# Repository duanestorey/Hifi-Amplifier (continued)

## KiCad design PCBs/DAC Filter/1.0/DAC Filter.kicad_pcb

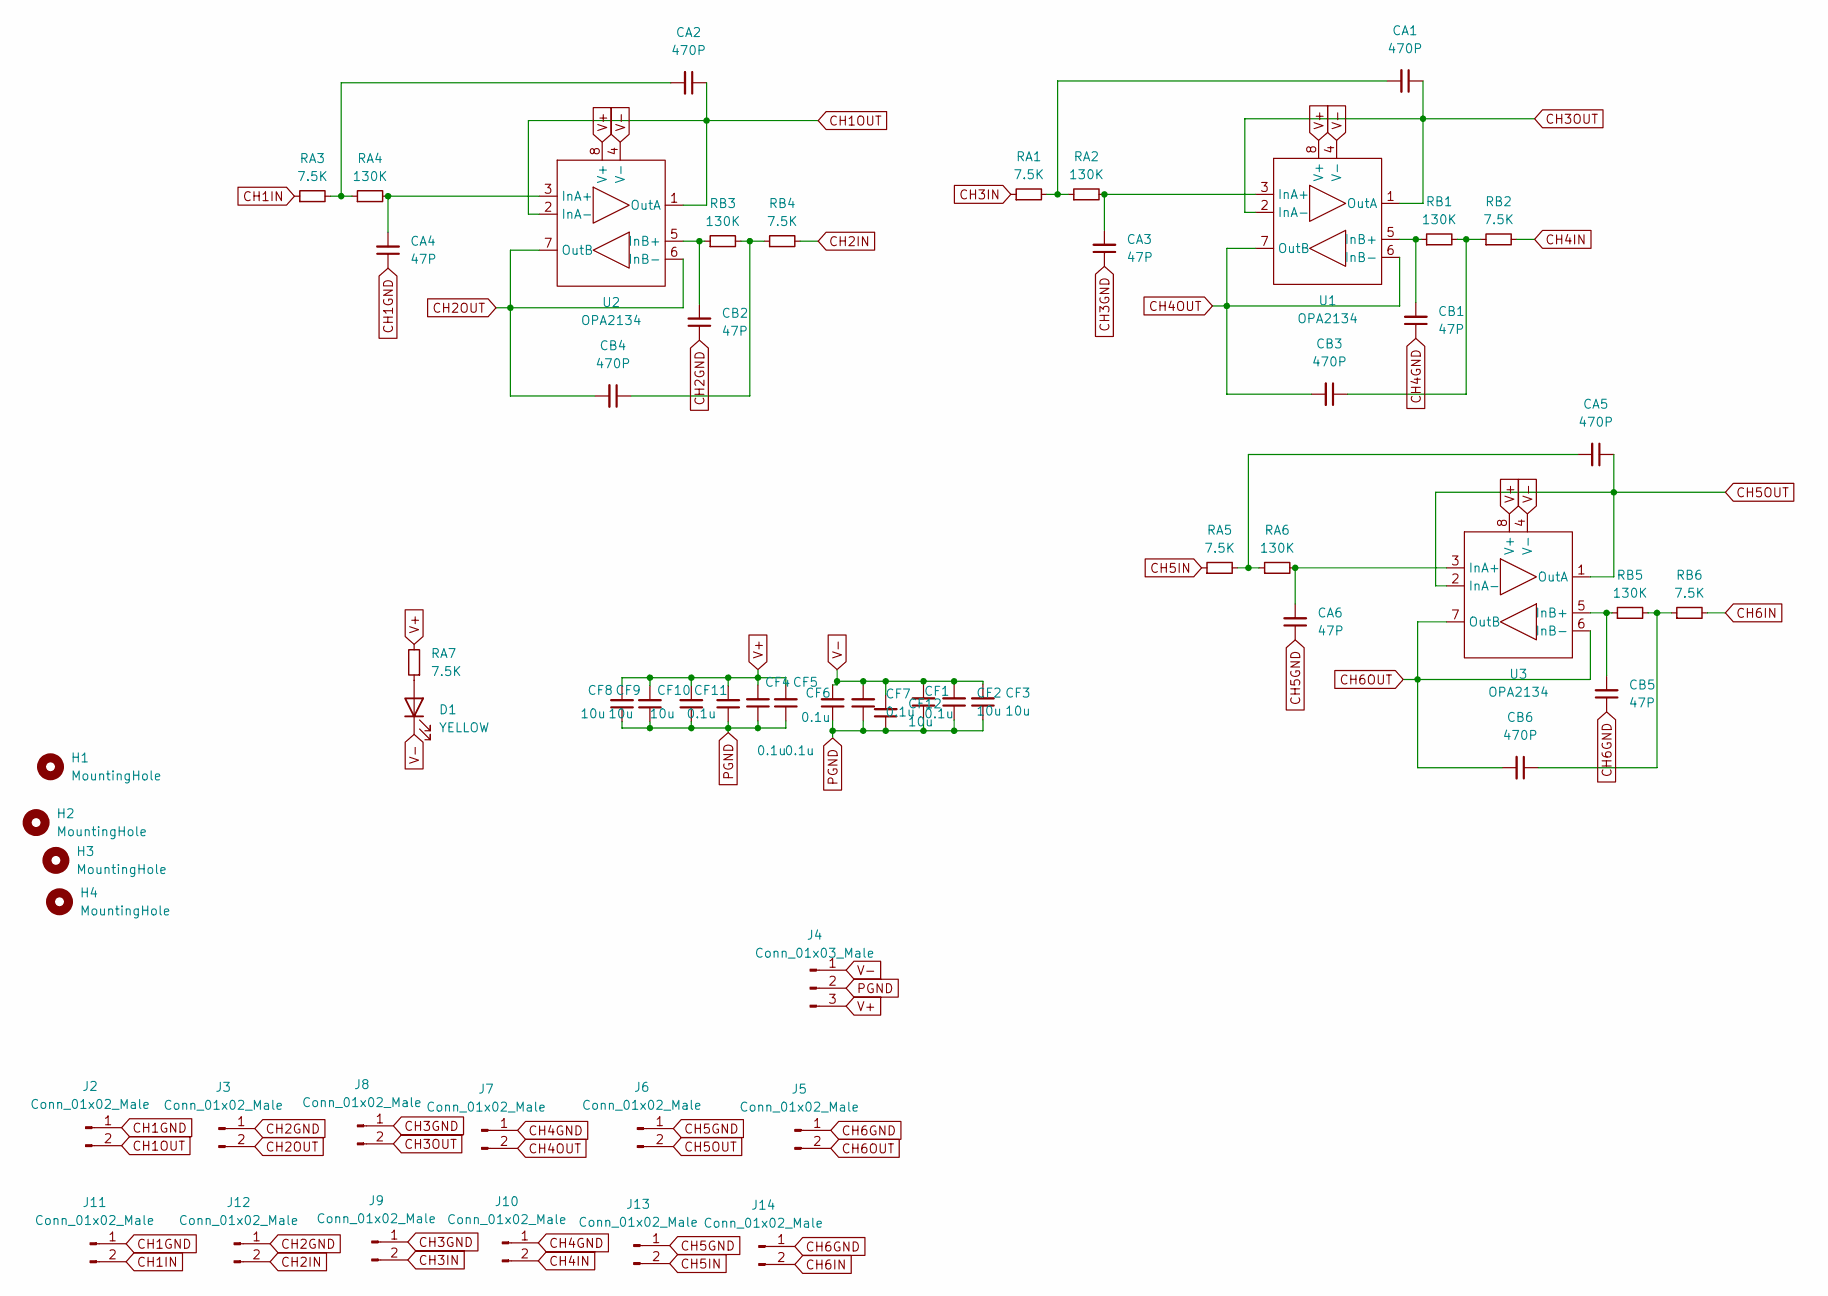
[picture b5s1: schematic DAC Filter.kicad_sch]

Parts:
CA1, CA2, CA5: 470P; C_1206_3216Metric_Pad1.33x1.80mm_HandSolder
CA3, CA4, CA6: 47P; C_1206_3216Metric_Pad1.33x1.80mm_HandSolder
CB1, CB2, CB5: 47P; C_1206_3216Metric_Pad1.33x1.80mm_HandSolder
CB3, CB4, CB6: 470P; C_1206_3216Metric_Pad1.33x1.80mm_HandSolder
CF1, CF4, CF5, CF6, CF7, CF11: 0.1u; C_0805_2012Metric_Pad1.18x1.45mm_HandSolder
CF2, CF3, CF8, CF9, CF10, CF12: 10u; C_1206_3216Metric_Pad1.33x1.80mm_HandSolder
D1: YELLOW; LED_0805_2012Metric_Pad1.15x1.40mm_HandSolder
H1, H2, H3, H4: MountingHole; MountingHole_3.2mm_M3
J2, J3, J5, J6, J7, J8, J9, J10, J11, J12, J13, J14: Conn_01x02_Male; JST_PH_B2B-PH-K_1x02_P2.00mm_Vertical
J4: Conn_01x03_Male; JST_PH_B3B-PH-K_1x03_P2.00mm_Vertical
RA1, RA3, RA5: 7.5K; R_1206_3216Metric_Pad1.30x1.75mm_HandSolder
RA2, RA4, RA6: 130K; R_1206_3216Metric_Pad1.30x1.75mm_HandSolder
RA7: 7.5K; R_0603_1608Metric
RB1, RB3, RB5: 130K; R_1206_3216Metric_Pad1.30x1.75mm_HandSolder
RB2, RB4, RB6: 7.5K; R_1206_3216Metric_Pad1.30x1.75mm_HandSolder
U1, U2, U3: OPA2134; DIP-8_W7.62mm_Socket

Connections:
CH1GND: CA4.1, J2.1, J11.1
CH1IN: J11.2, RA3.1
CH1OUT: CA2.1, J2.2, U2.1 (OutA), U2.2 (InA-)
CH2GND: CB2.1, J3.1, J12.1
CH2IN: J12.2, RB4.2
CH2OUT: CB4.2, J3.2, U2.6 (InB-), U2.7 (OutB)
CH3GND: CA3.1, J8.1, J9.1
CH3IN: J9.2, RA1.1
CH3OUT: CA1.1, J8.2, U1.1 (OutA), U1.2 (InA-)
CH4GND: CB1.1, J7.1, J10.1
CH4IN: J10.2, RB2.2
CH4OUT: CB3.2, J7.2, U1.6 (InB-), U1.7 (OutB)
CH5GND: CA6.1, J6.1, J13.1
CH5IN: J13.2, RA5.1
CH5OUT: CA5.1, J6.2, U3.1 (OutA), U3.2 (InA-)
CH6GND: CB5.1, J5.1, J14.1
CH6IN: J14.2, RB6.2
CH6OUT: CB6.2, J5.2, U3.6 (InB-), U3.7 (OutB)
unnamed: CA1.2, RA1.2, RA2.1
unnamed: CA2.2, RA3.2, RA4.1
unnamed: CA3.2, RA2.2, U1.3 (InA+)
unnamed: CA4.2, RA4.2, U2.3 (InA+)
unnamed: CA5.2, RA5.2, RA6.1
unnamed: CA6.2, RA6.2, U3.3 (InA+)
unnamed: CB1.2, RB1.1, U1.5 (InB+)
unnamed: CB2.2, RB3.1, U2.5 (InB+)
unnamed: CB3.1, RB1.2, RB2.1
unnamed: CB4.1, RB3.2, RB4.1
unnamed: CB5.2, RB5.1, U3.5 (InB+)
unnamed: CB6.1, RB5.2, RB6.1
unnamed: D1.2 (A), RA7.1
PGND: CF1.1, CF2.1, CF3.1, CF4.1, CF5.1, CF6.1, CF7.1, CF8.1, CF9.1, CF10.1, CF11.1, CF12.1, J4.2
V+: CF4.2, CF5.2, CF8.2, CF9.2, CF10.2, CF11.2, J4.3, RA7.2, U1.8 (V+), U2.8 (V+), U3.8 (V+)
V-: CF1.2, CF2.2, CF3.2, CF6.2, CF7.2, CF12.2, D1.1 (K), J4.1, U1.4 (V-), U2.4 (V-), U3.4 (V-)

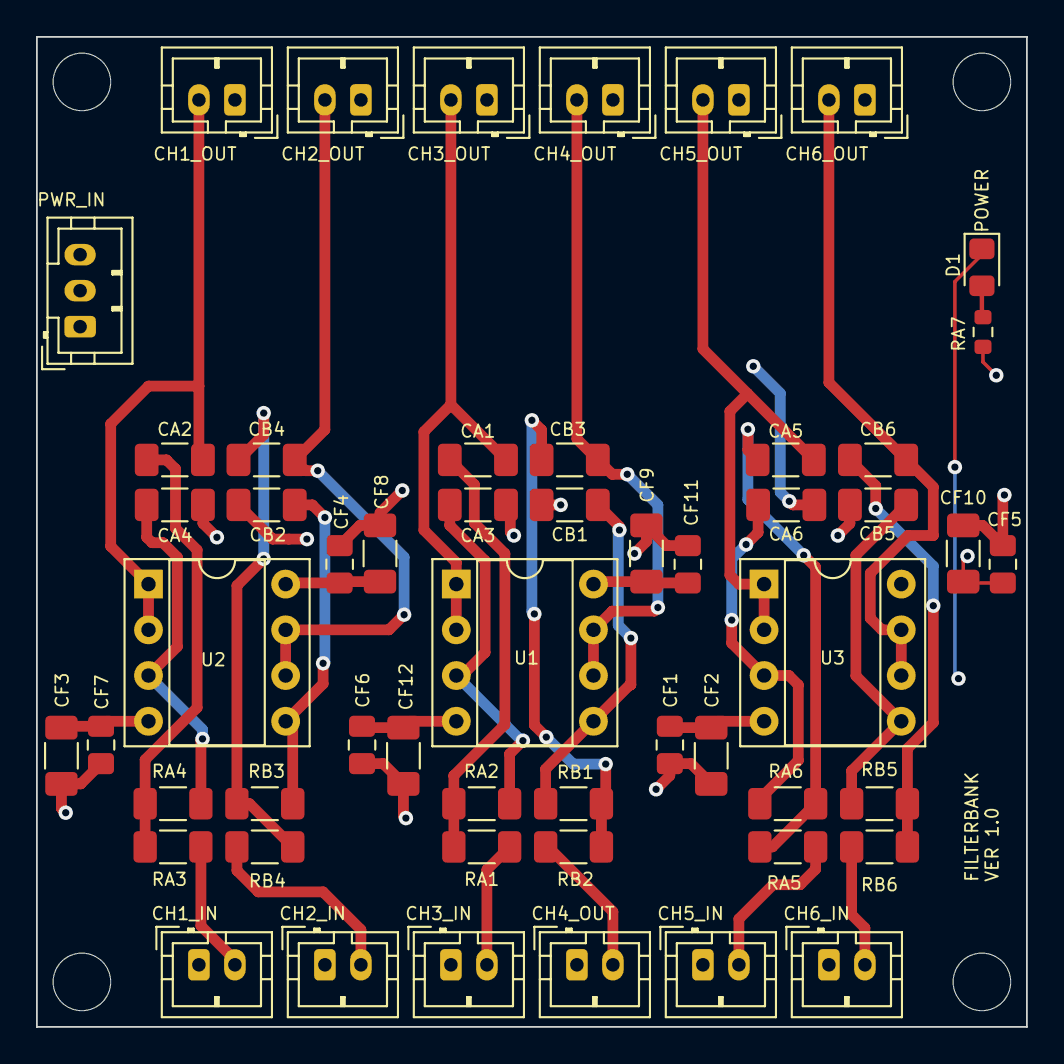
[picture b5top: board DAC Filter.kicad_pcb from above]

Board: 4 copper layers, 55.0 x 55.0 mm, 58 parts (0 on the bottom side), 34 nets.
